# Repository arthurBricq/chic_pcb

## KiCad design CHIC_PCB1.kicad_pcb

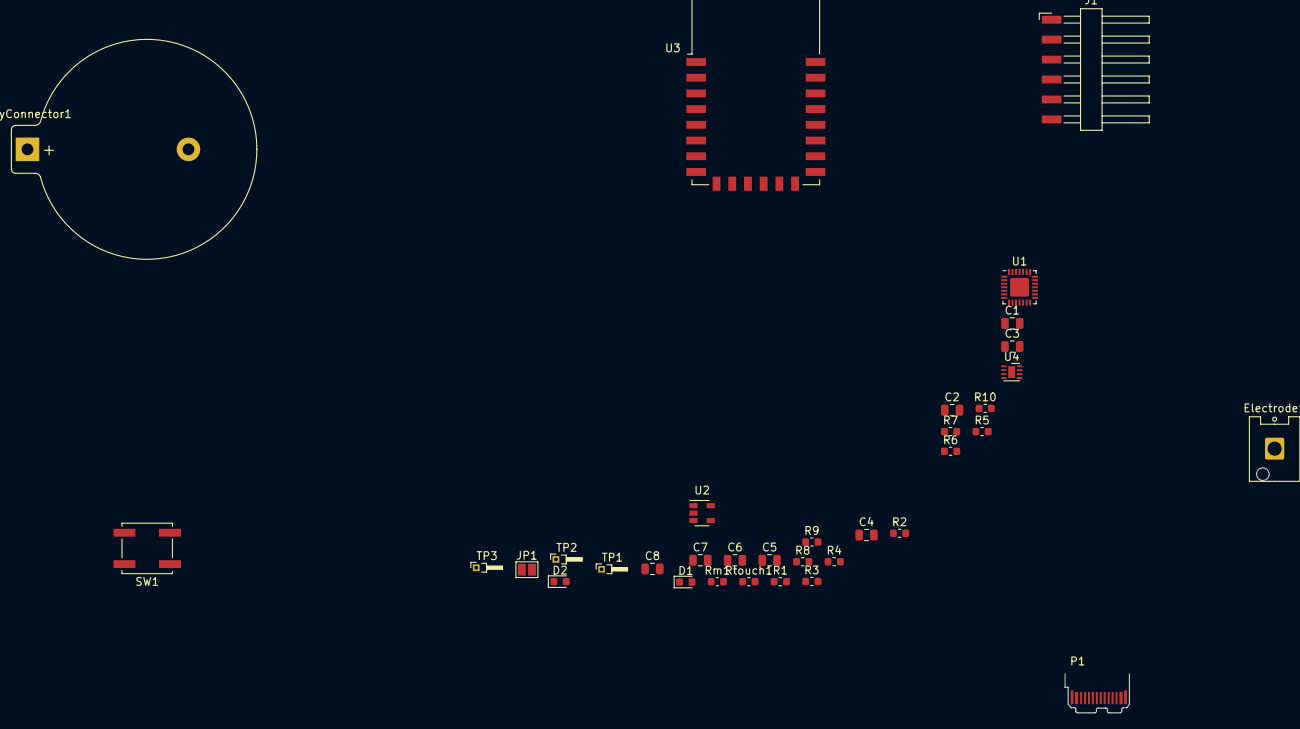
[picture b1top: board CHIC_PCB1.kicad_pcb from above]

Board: 2 copper layers, 39 parts (0 on the bottom side), 22 nets, no tracks yet.

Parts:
BatteryConnector1: Conn_01x0; BatteryHolder_Keystone_106_1x20mm
C1, C2: 10u; C_0805_2012Metric
C3, C4: 100n; C_0805_2012Metric
C5: 100nF; C_0805_2012Metric
C6, C8: C; C_0805_2012Metric
C7: 0.1u; C_0805_2012Metric
D1, D2: LED; LED_0603_1608Metric
Electrode1: Conn_01x01; Hirose_DF63M-1P-3.96DSA_1x01_P3.96mm_Vertical
H1, H2, H3, H4: MountingHole; MountingHole_3.2mm_M3
J1: Conn_01x06_Female; Harwin_M20-89006xx_1x06_P2.54mm_Horizontal
JP1: Jumper; SolderJumper-2_P1.3mm_Open_Pad1.0x1.5mm
P1: USB_C_Plug_USB2.0; USB_C_Plug_JAE_DX07P024AJ1
R1, R2: 470; R_0603_1608Metric
R3, R4: 2.0k; R_0603_1608Metric
R5, R6, R9, R10: 10k; R_0603_1608Metric
R7, R8: R; R_0603_1608Metric
Rm1: R; R_0603_1608Metric
Rtouch1: R; R_0603_1608Metric
SW1: SW_Push; SW_Push_1P1T_NO_CK_KSC7xxJ
TP1, TP2, TP3: TestPoint; PinHeader_1x01_P1.00mm_Horizontal
U1: ATmega328P-MMH; QFN-28-1EP_4x4mm_P0.45mm_EP2.4x2.4mm
U2: MCP73831-2-OT; SOT-23-5
U3: ESP-12E
U4: AT42QT1010-M; DFN-8-1EP_2x2mm_P0.5mm_EP0.9x1.5mm

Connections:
+3V3: C5.1, U4.7
/MC_RX: TP2.1, U1.26, U3.16
/MC_TX: TP1.1, U1.27, U3.15
/Vtouch: Rtouch1.2, TP3.1, U1.19
/rst: C7.2, C8.1, R7.2, SW1.1
GND: BatteryConnector1.2, C1.2, C2.2, C3.2, C4.2, C5.2, C8.2, D2.1, P1.A1, P1.A12, P1.B1, P1.B12, R3.2, R4.1, R10.2, Rm1.2, SW1.2, U1.4, U1.18, U1.29, U2.2, U3.9, U4.4, U4.6, U4.9
unnamed: C1.1, P1.A4, P1.A9, P1.B4, P1.B9, U2.4
unnamed: C6.1, R8.2, U4.1
unnamed: C6.2, Rm1.1, U4.8
unnamed: C7.1, U1.25
unnamed: D1.1, R1.2
unnamed: D2.2, R2.2
unnamed: Electrode1.1, R8.1
unnamed: JP1.1, R3.1, U2.5
unnamed: JP1.2, R4.2
unnamed: R1.1, R2.1, U2.1
unnamed: R5.1, U3.1
unnamed: R6.1, U3.3
unnamed: R9.2, U3.12
unnamed: R10.1, U3.10
unnamed: Rtouch1.1, U4.5
VCC: BatteryConnector1.1, C2.1, C3.1, C4.1, R5.2, R6.2, R7.1, R9.1, U1.3, U2.3, U3.8

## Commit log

2020-04-26 This is the first commit before starting to change the schematic (removing the atmega)
2020-04-26 Second version finished, to be verified
2020-04-26 Test de github
2020-04-26 Corrected touch sensor circuit. Added capacitor value.
